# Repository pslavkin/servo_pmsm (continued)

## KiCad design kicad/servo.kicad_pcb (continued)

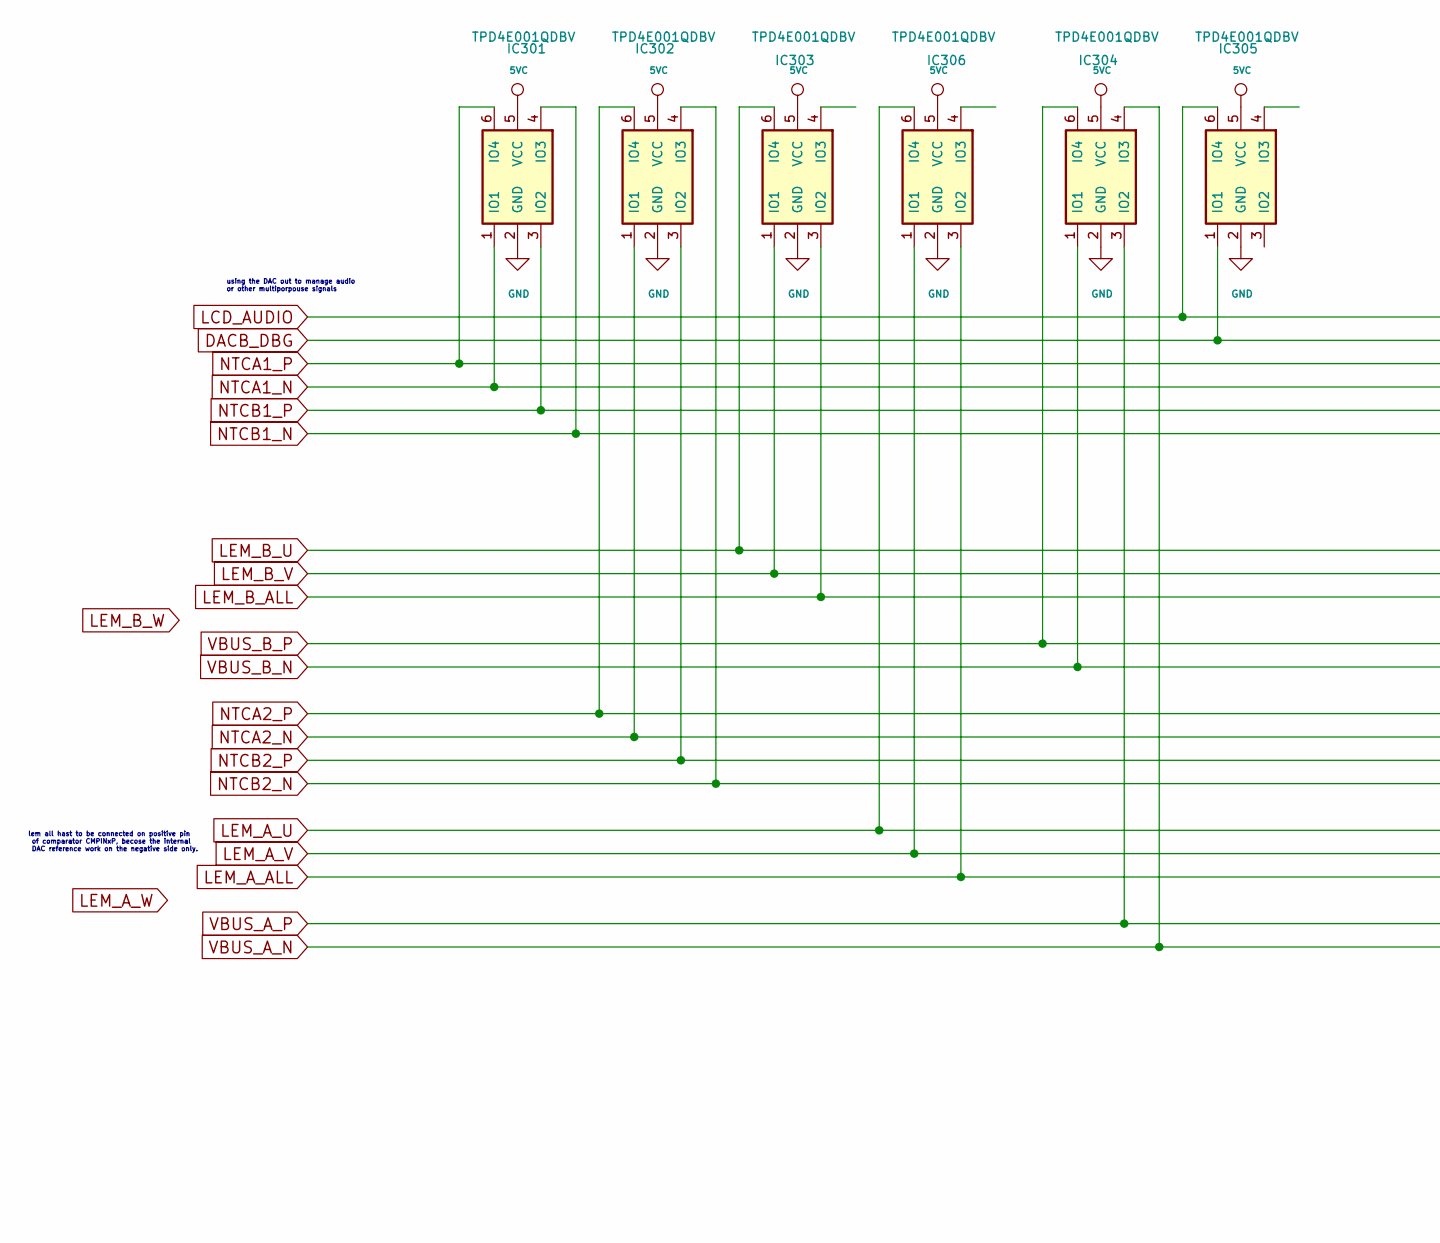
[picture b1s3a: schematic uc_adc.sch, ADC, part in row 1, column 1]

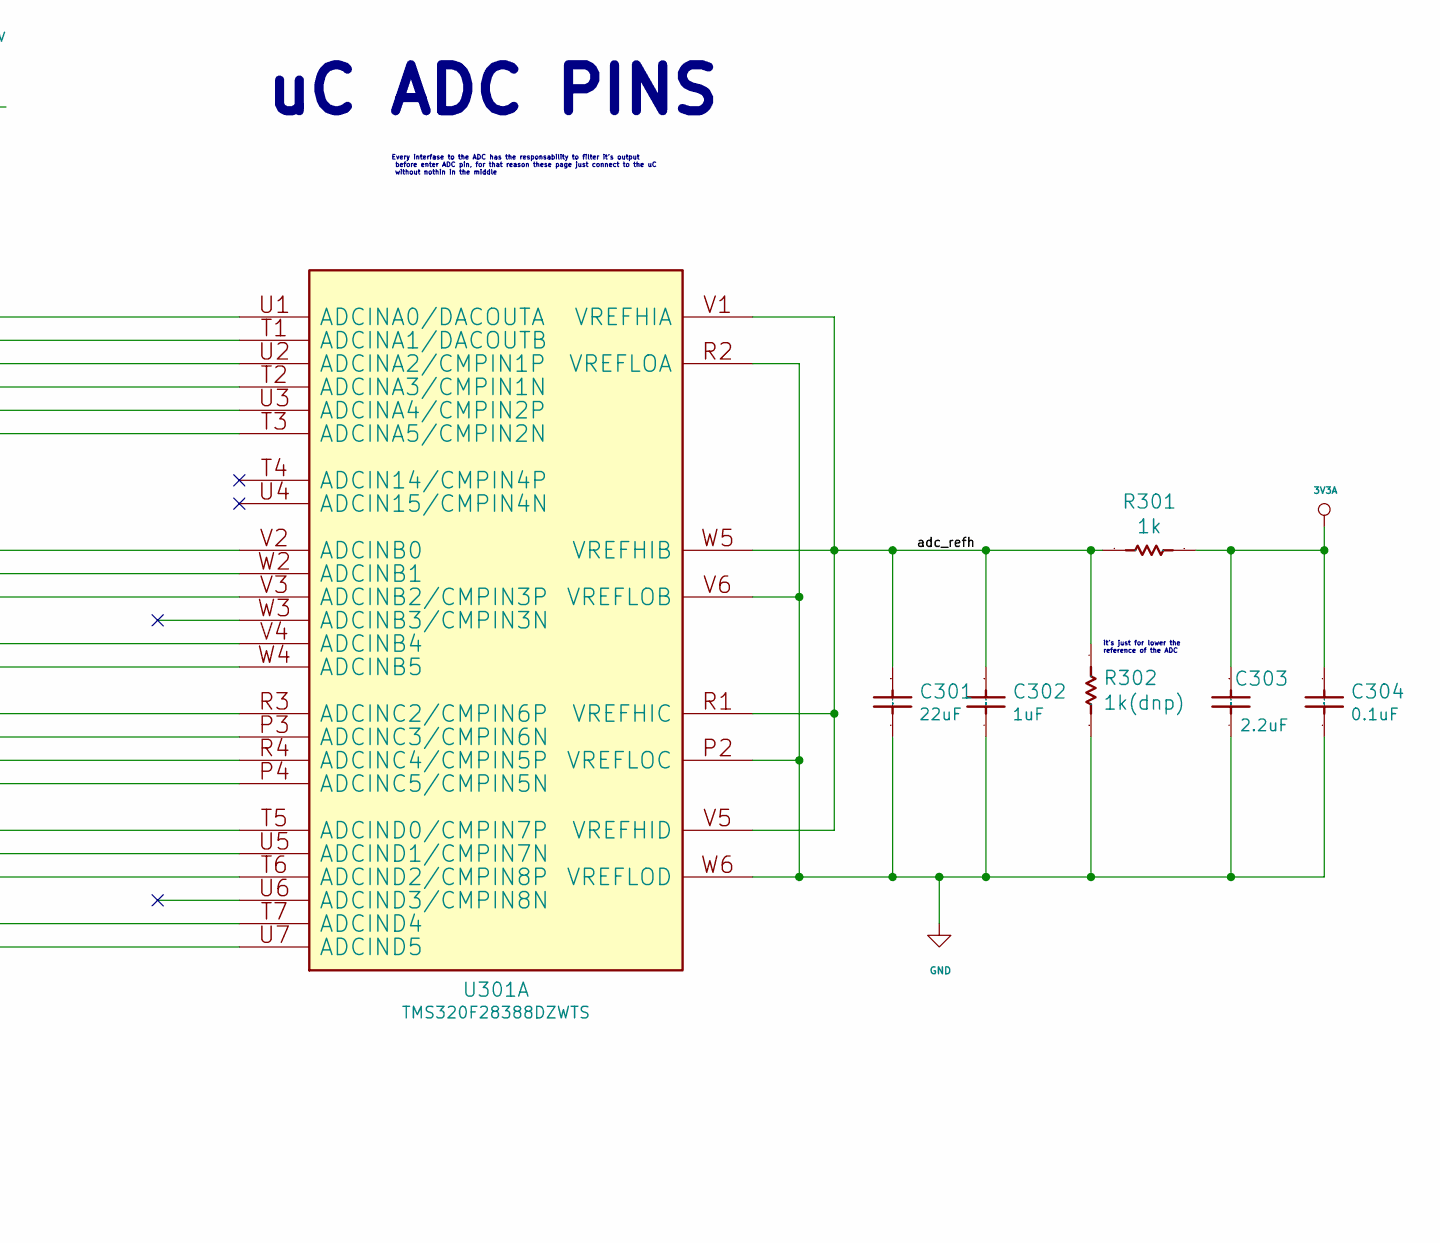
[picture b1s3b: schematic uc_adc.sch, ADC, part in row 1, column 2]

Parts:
C301: 22uF; C_0603_1608Metric
C302: 1uF; C_0603_1608Metric
C303: 2.2uF; C_0603_1608Metric
C304: 0.1uF; C_0603_1608Metric
IC301, IC302, IC303, IC304, IC305, IC306: TPD4E001QDBV; SOT-23-6
R301: 1k; R_0603_1608Metric
R302: 1k(dnp); R_0603_1608Metric
U301: TMS320F28388DZWTS; BGA337CP80_19X19_1600X1600X140B50N; PartNumber TMS320F28388DZWTS

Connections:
3V3A: C303.1, C304.1, R301.1; also elsewhere on the board
5VC: IC301.5 (VCC), IC302.5 (VCC), IC303.5 (VCC), IC304.5 (VCC), IC305.5 (VCC), IC306.5 (VCC); also elsewhere on the board
/uc_adc/adc_refh: C301.1, C302.1, R301.2, R302.2, U301.R1 (VREFHIC), U301.V1 (VREFHIA), U301.V5 (VREFHID), U301.W5 (VREFHIB)
DACB_DBG: IC305.1 (IO1), U301.T1 (ADCINA1/DACOUTB); also elsewhere on the board
GND: C301.2 (Capacitor), C302.2 (Capacitor), C303.2 (Capacitor), C304.2 (Capacitor), IC301.2 (GND), IC302.2 (GND), IC303.2 (GND), IC304.2 (GND), IC305.2 (GND), IC306.2 (GND), R302.1, U301.P2 (VREFLOC), U301.R2 (VREFLOA), U301.V6 (VREFLOB), U301.W6 (VREFLOD); also elsewhere on the board
LCD_AUDIO: IC305.6 (IO4), U301.U1 (ADCINA0/DACOUTA); also elsewhere on the board
LEM_A_ALL: IC306.3 (IO2), U301.T6 (ADCIND2/CMPIN8P); also elsewhere on the board
LEM_A_U: IC306.6 (IO4), U301.T5 (ADCIND0/CMPIN7P); also elsewhere on the board
LEM_A_V: IC306.1 (IO1), U301.U5 (ADCIND1/CMPIN7N); also elsewhere on the board
LEM_B_ALL: IC303.3 (IO2), U301.V3 (ADCINB2/CMPIN3P); also elsewhere on the board
LEM_B_U: IC303.6 (IO4), U301.V2 (ADCINB0); also elsewhere on the board
LEM_B_V: IC303.1 (IO1), U301.W2 (ADCINB1); also elsewhere on the board
NTCA1_N: IC301.1 (IO1), U301.T2 (ADCINA3/CMPIN1N); also elsewhere on the board
NTCA1_P: IC301.6 (IO4), U301.U2 (ADCINA2/CMPIN1P); also elsewhere on the board
NTCA2_N: IC302.1 (IO1), U301.P3 (ADCINC3/CMPIN6N); also elsewhere on the board
NTCA2_P: IC302.6 (IO4), U301.R3 (ADCINC2/CMPIN6P); also elsewhere on the board
NTCB1_N: IC301.4 (IO3), U301.T3 (ADCINA5/CMPIN2N); also elsewhere on the board
NTCB1_P: IC301.3 (IO2), U301.U3 (ADCINA4/CMPIN2P); also elsewhere on the board
NTCB2_N: IC302.4 (IO3), U301.P4 (ADCINC5/CMPIN5N); also elsewhere on the board
NTCB2_P: IC302.3 (IO2), U301.R4 (ADCINC4/CMPIN5P); also elsewhere on the board
VBUS_A_N: IC304.4 (IO3), U301.U7 (ADCIND5); also elsewhere on the board
VBUS_A_P: IC304.3 (IO2), U301.T7 (ADCIND4); also elsewhere on the board
VBUS_B_N: IC304.1 (IO1), U301.W4 (ADCINB5); also elsewhere on the board
VBUS_B_P: IC304.6 (IO4), U301.V4 (ADCINB4); also elsewhere on the board

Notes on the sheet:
lem all hast to be connected on positive pin of comparator CMPINxP, becose the internal DAC reference work on the negative side only.
uC ADC PINS
Every interfase to the ADC has the responsability to filter it's output before enter ADC pin, for that reason these page just connect to the uC without nothin in the middle
using the DAC out to manage audio or other multiporpouse signals
it's just for lower the reference of the ADC

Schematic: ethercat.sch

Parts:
C401, C402, C416, C417: 0.01uF; C_0603_1608Metric
C403, C404, C413, C414, C415, C418, C419, C422, C423: 0.1uF; C_0603_1608Metric
C405, C406, C411, C412, C420, C421, C424, C425, C426, C427, C428, C429, C430, C431, C432, C433: 1uF; C_0603_1608Metric
C407, C408, C409, C410: 10uF; C_0603_1608Metric
C434: 4n7; C_1206_3216Metric
D401: Red@2mA; LED_0603_1608Metric
D402: green@2mA; LED_0603_1608Metric
R401, R402, R403, R404, R405, R406, R407, R408, R409, R410, R411, R412, R413, R414, R415, R416, R427, R433, R434: 2.2k; R_0603_1608Metric
R417, R418: 4.7k; R_0603_1608Metric
R419, R420: 330; R_0603_1608Metric
R421, R424: 4.87k; R_0603_1608Metric
R422, R425: 10.0k; R_0603_1608Metric
R423, R426: 0e; R_0603_1608Metric
R429, R430, R431, R432, R435, R437, R438, R440: 49.9; R_0603_1608Metric
R436, R439: 0e(dnp); R_0603_1608Metric
R441, R442, R445, R446: 470; R_0603_1608Metric
U401: CAT24C16WI; SOIC-8_3.9x4.9mm_P1.27mm
U402, U403: DP83822; QFN-32-1EP_5x5mm_P0.5mm_EP2.9x2.9mm_ThermalVias; PartNumber DP83822IRHBR
U404: rj45x2; rj45x2_0845-2G1T-H5
Y401, Y402: dnp; Oscillator_SMD_SeikoEpson_SG210-4Pin_2.5x2.0mm

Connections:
3V3: C401.2 (Capacitor), C402.2 (Capacitor), C403.2 (Capacitor), C404.2 (Capacitor), C405.1, C406.1, C407.1, C408.1, C409.1, C410.1, C411.1, C412.1, C413.1, C414.1, C415.1, C416.1, C417.1, C418.1, C419.1, C420.1, C421.1, C422.1, C423.1, C424.1, C425.1, C426.2 (Capacitor), C427.2 (Capacitor), C428.2 (Capacitor), C429.2 (Capacitor), C430.2 (Capacitor), C431.2 (Capacitor), C432.2 (Capacitor), C433.2 (Capacitor), R412.1, R413.1, R414.1, R415.1, R416.1, R417.1, R418.1, R419.2, R420.2, R422.2, R425.2, R427.1, R429.1, R430.1, R431.1, R432.1, R433.1, R434.1, R435.1, R437.1, R438.1, R440.1, R441.1, R442.1, R445.1, R446.1, U401.8 (VCC), U402.14 (AVD33), U402.21 (VDDIO), U403.14 (AVD33), U403.21 (VDDIO), U404.2 (TCT), U404.5 (TCT), U404.9 (TCT), U404.12 (TCT), Y401.1 (TRI-STATE), Y401.4 (VCC), Y402.2 (GND), Y402.3 (OUTPUT); also elsewhere on the board
/ethercat/P0_RD_N: R437.2, U402.9 (RD_M), U404.13 (RD-)
/ethercat/P0_RD_P: R435.2, U402.10 (RD_P), U404.11 (RD+)
/ethercat/P0_TD_N: R431.2, U402.11 (TD_M), U404.10 (TD-)
/ethercat/P0_TD_P: R429.2, U402.12 (TD_P), U404.8 (TD+)
/ethercat/P1_RD_N: R440.2, U403.9 (RD_M), U404.6 (RD-)
/ethercat/P1_RD_P: R438.2, U403.10 (RD_P), U404.4 (RD+)
/ethercat/P1_TD_N: R432.2, U403.11 (TD_M), U404.3 (TD-)
/ethercat/P1_TD_P: R430.2, U403.12 (TD_P), U404.1 (TD+)
/ethercat/ecat0_col: R410.2, U402.29 (COL/PHYAD0/MLED)
/ethercat/ecat0_crs: R413.2, U402.27 (CRS/CRS_DV/LED_CFG)
/ethercat/ecat1_col: R412.2, U403.29 (COL/PHYAD0/MLED)
/ethercat/ecat1_crs: R414.2, U403.27 (CRS/CRS_DV/LED_CFG)
ECAT0_RJ_LED0: R436.2, U404.20 (Led-); also elsewhere on the board
ECAT0_RJ_LED1: U404.22 (Led-); also elsewhere on the board
ECAT0_RX_CLK: U402.25 (RX_CLK); also elsewhere on the board
ECAT0_RX_D0: R402.2, U402.30 (RX_D0/PHYAD1); also elsewhere on the board
ECAT0_RX_D1: R404.2, U402.31 (RX_D1/PHYAD2); also elsewhere on the board
ECAT0_RX_D2: R406.2, U402.32 (RX_D2/PHYAD3); also elsewhere on the board
ECAT0_RX_D3: R408.2, U402.1 (RX_D3/PHYAD4/CLKOUT); also elsewhere on the board
ECAT0_RX_DV: R401.2, U402.26 (RX_DV/MII_MODE); also elsewhere on the board
ECAT0_RX_ER: R415.2, U402.28 (RX_ER/AMDIX_EN); also elsewhere on the board
ECAT0_TX_CLK: U402.2 (TX_CLK); also elsewhere on the board
ECAT0_TX_D0: U402.4 (TX_D0); also elsewhere on the board
ECAT0_TX_D1: U402.5 (TX_D1); also elsewhere on the board
ECAT0_TX_D2: U402.6 (TX_D2); also elsewhere on the board
ECAT0_TX_D3: U402.7 (TX_D3); also elsewhere on the board
ECAT0_TX_EN: U402.3 (TX_EN); also elsewhere on the board
ECAT1_RJ_LED0: U404.18 (Led-); also elsewhere on the board
ECAT1_RJ_LED1: R439.2, U404.16 (Led-); also elsewhere on the board
ECAT1_RX_CLK: U403.25 (RX_CLK); also elsewhere on the board
ECAT1_RX_D0: R405.2, U403.30 (RX_D0/PHYAD1); also elsewhere on the board
ECAT1_RX_D1: R407.2, U403.31 (RX_D1/PHYAD2); also elsewhere on the board
ECAT1_RX_D2: R409.2, U403.32 (RX_D2/PHYAD3); also elsewhere on the board
ECAT1_RX_D3: R411.2, U403.1 (RX_D3/PHYAD4/CLKOUT); also elsewhere on the board
ECAT1_RX_DV: R403.2, U403.26 (RX_DV/MII_MODE); also elsewhere on the board
ECAT1_RX_ER: R416.2, U403.28 (RX_ER/AMDIX_EN); also elsewhere on the board
ECAT1_TX_CLK: U403.2 (TX_CLK); also elsewhere on the board
ECAT1_TX_D0: U403.4 (TX_D0); also elsewhere on the board
ECAT1_TX_D1: U403.5 (TX_D1); also elsewhere on the board
ECAT1_TX_D2: U403.6 (TX_D2); also elsewhere on the board
ECAT1_TX_D3: U403.7 (TX_D3); also elsewhere on the board
ECAT1_TX_EN: U403.3 (TX_EN); also elsewhere on the board
ECAT_EEPROM_SCL: R418.2, U401.6 (SCL); also elsewhere on the board
ECAT_EEPROM_SDA: R417.2, U401.5 (SDA); also elsewhere on the board
ECAT_LED_ERR: D402.1 (K); also elsewhere on the board
ECAT_LED_RUN: D401.1 (K); also elsewhere on the board
ECAT_MDCLK: U402.20 (MDC), U403.20 (MDC); also elsewhere on the board
ECAT_MDIO: R427.2, U402.19 (MDIO), U403.19 (MDIO); also elsewhere on the board
ECAT_RST: U402.18 (RESET), U403.18 (RESET); also elsewhere on the board
ENET_CAT_XI: R423.2, R426.2; also elsewhere on the board
Earth: C434.2 (Capacitor), U404.7 (Gnd), U404.14 (Gnd); also elsewhere on the board
GND: C401.1, C402.1, C403.1, C404.1, C405.2 (Capacitor), C406.2 (Capacitor), C407.2 (Capacitor), C408.2 (Capacitor), C409.2 (Capacitor), C410.2 (Capacitor), C411.2 (Capacitor), C412.2 (Capacitor), C413.2 (Capacitor), C414.2 (Capacitor), C415.2 (Capacitor), C416.2 (Capacitor), C417.2 (Capacitor), C418.2 (Capacitor), C419.2 (Capacitor), C420.2 (Capacitor), C421.2 (Capacitor), C422.2 (Capacitor), C423.2 (Capacitor), C424.2 (Capacitor), C425.2 (Capacitor), C426.1, C427.1, C428.1, C429.1, C430.1, C431.1, C432.1, C433.1, C434.1, R401.1, R402.1, R403.1, R404.1, R405.1, R406.1, R407.1, R408.1, R409.1, R410.1, R411.1, R421.2, R424.2, U401.1 (NC), U401.2 (NC), U401.3 (NC), U401.4 (VSS), U401.7 (WP), U402.33 (PAD), U403.33 (PAD), Y401.2 (GND), Y402.1 (TRI-STATE); also elsewhere on the board
unnamed: D401.2 (A), R419.1
unnamed: D402.2 (A), R420.1
unnamed: R421.1, U402.16 (RBIAS)
unnamed: R422.1, U402.8 (INT/~PWDN)
unnamed: R423.1, U402.23 (XI), Y401.3 (OUTPUT)
unnamed: R424.1, U403.16 (RBIAS)
unnamed: R425.1, U403.8 (INT/~PWDN)
unnamed: R426.1, U403.23 (XI), Y402.4 (VCC)
unnamed: R433.2, R436.1, U402.17 (LED_0/AN_0/MLED)
unnamed: R434.2, R439.1, U403.17 (LED_0/AN_0/MLED)
unnamed: R441.2, U404.17 (Led+)
unnamed: R442.2, U404.15 (Led+)
unnamed: R445.2, U404.21 (Led+)
unnamed: R446.2, U404.19 (Led+)

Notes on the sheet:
EtherCAT P1
EtherCAT EEPROM
Run and Error LEDs
EtherCAT P0
Address select. Be shure you select two distinct
these IC is a 'must'. Especified on the ethercat slave
EtherCAT
you could choose between uC out clk, oscilator for ecah PHY or share oscilator to many PHY's using uC out clk path
the pullup of led_0 is mandatory, but to drive the led you could choose between PHY or uC populating/unpopulating the resistor
It'd be optionall
I choose transfeormer spare part instead of the embedded shielded RJ45 plus leds, cause noy I can choose any format connector RJ45 and maybe add PoE then. And are halt the price The eeprom is mandatory in order to ESC read save some internal configuration. Leds are optional, but the PHY's has som p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
2k2 pullup as indicated by phy IC's
25Mhz!!
It's a good idea to have them on these fitst stage but could be throught away on next release.

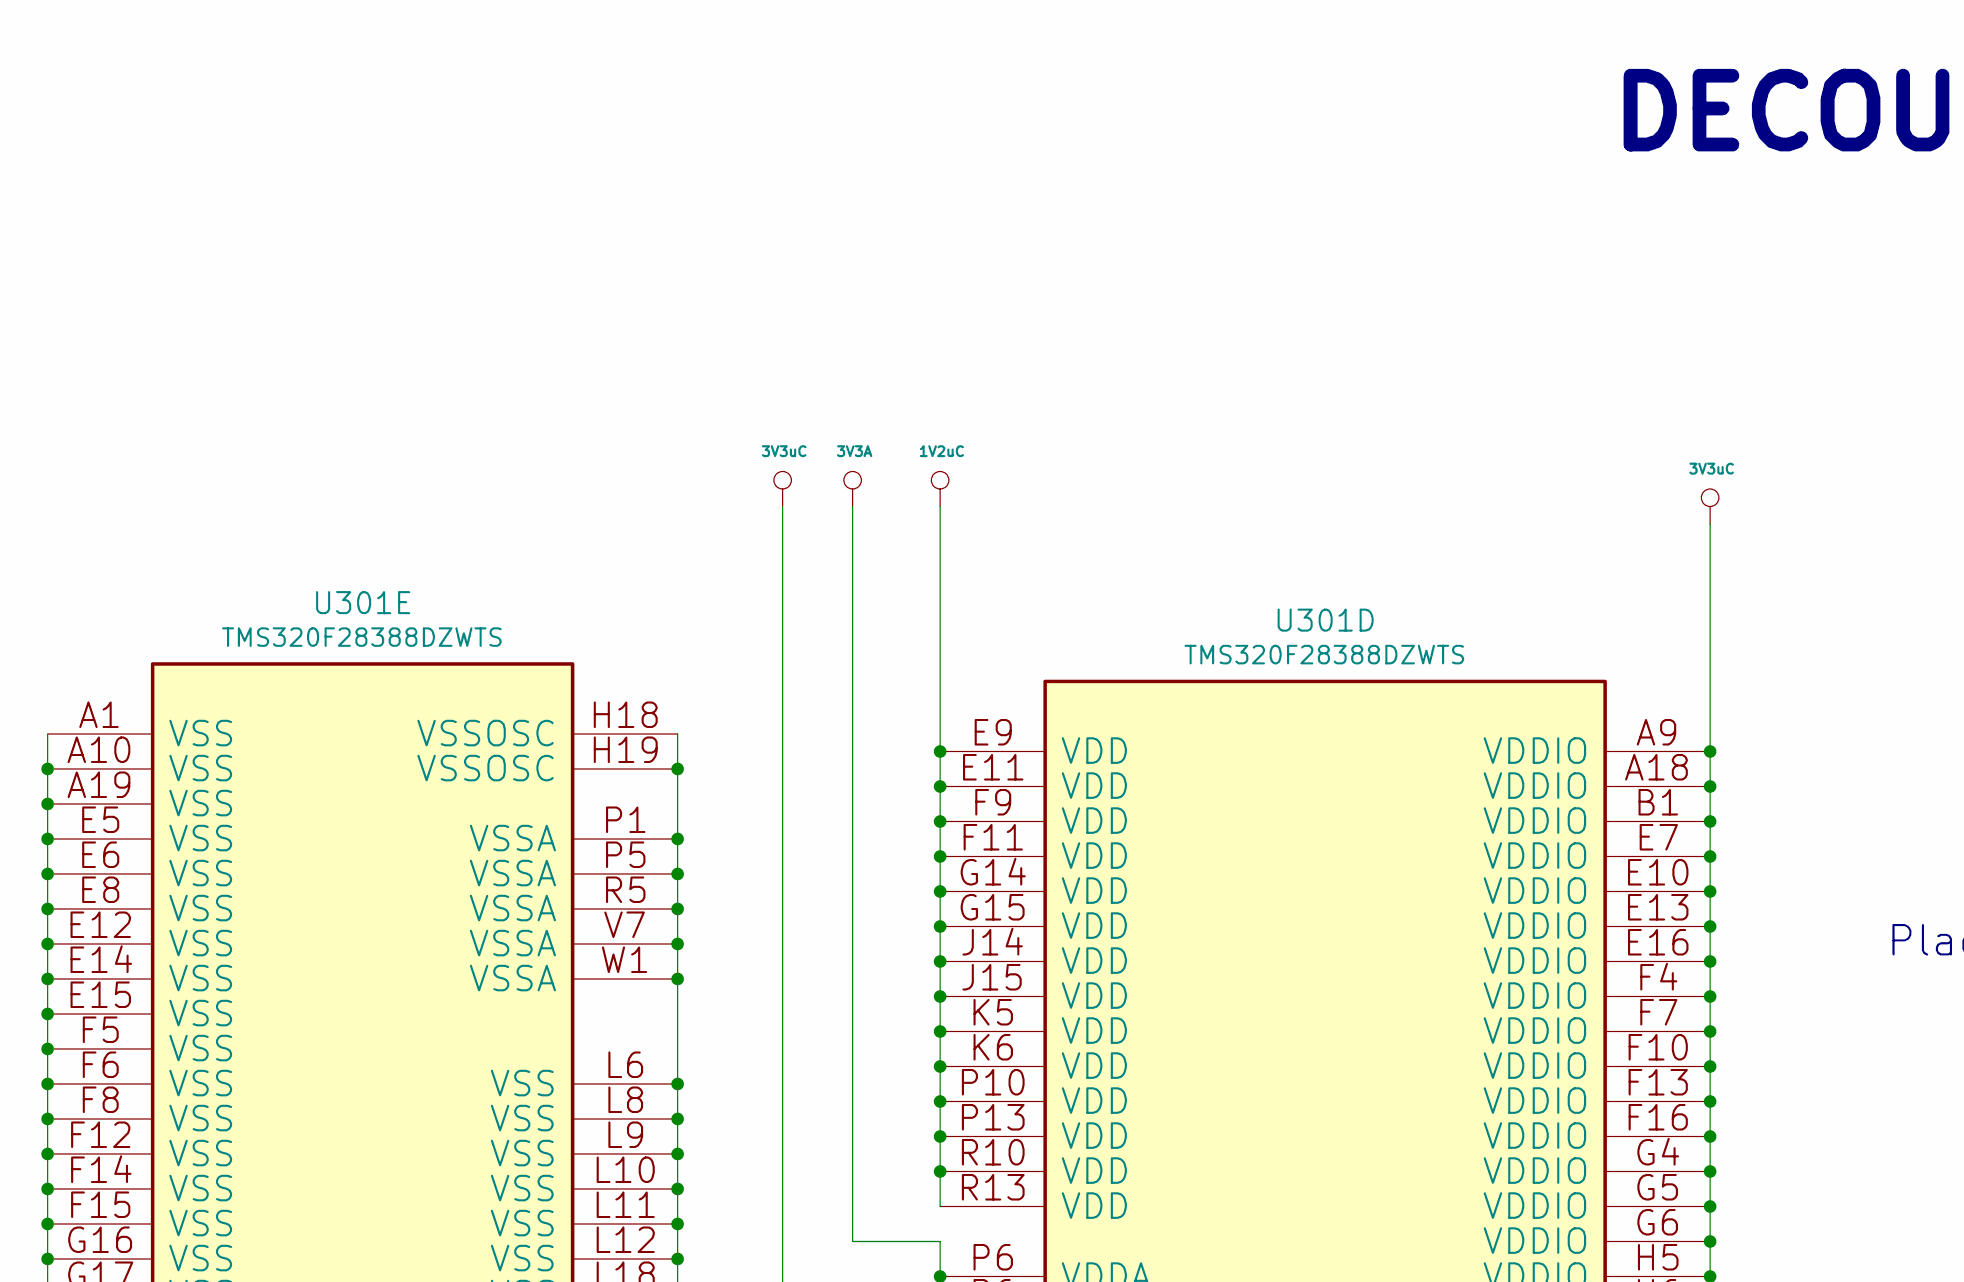
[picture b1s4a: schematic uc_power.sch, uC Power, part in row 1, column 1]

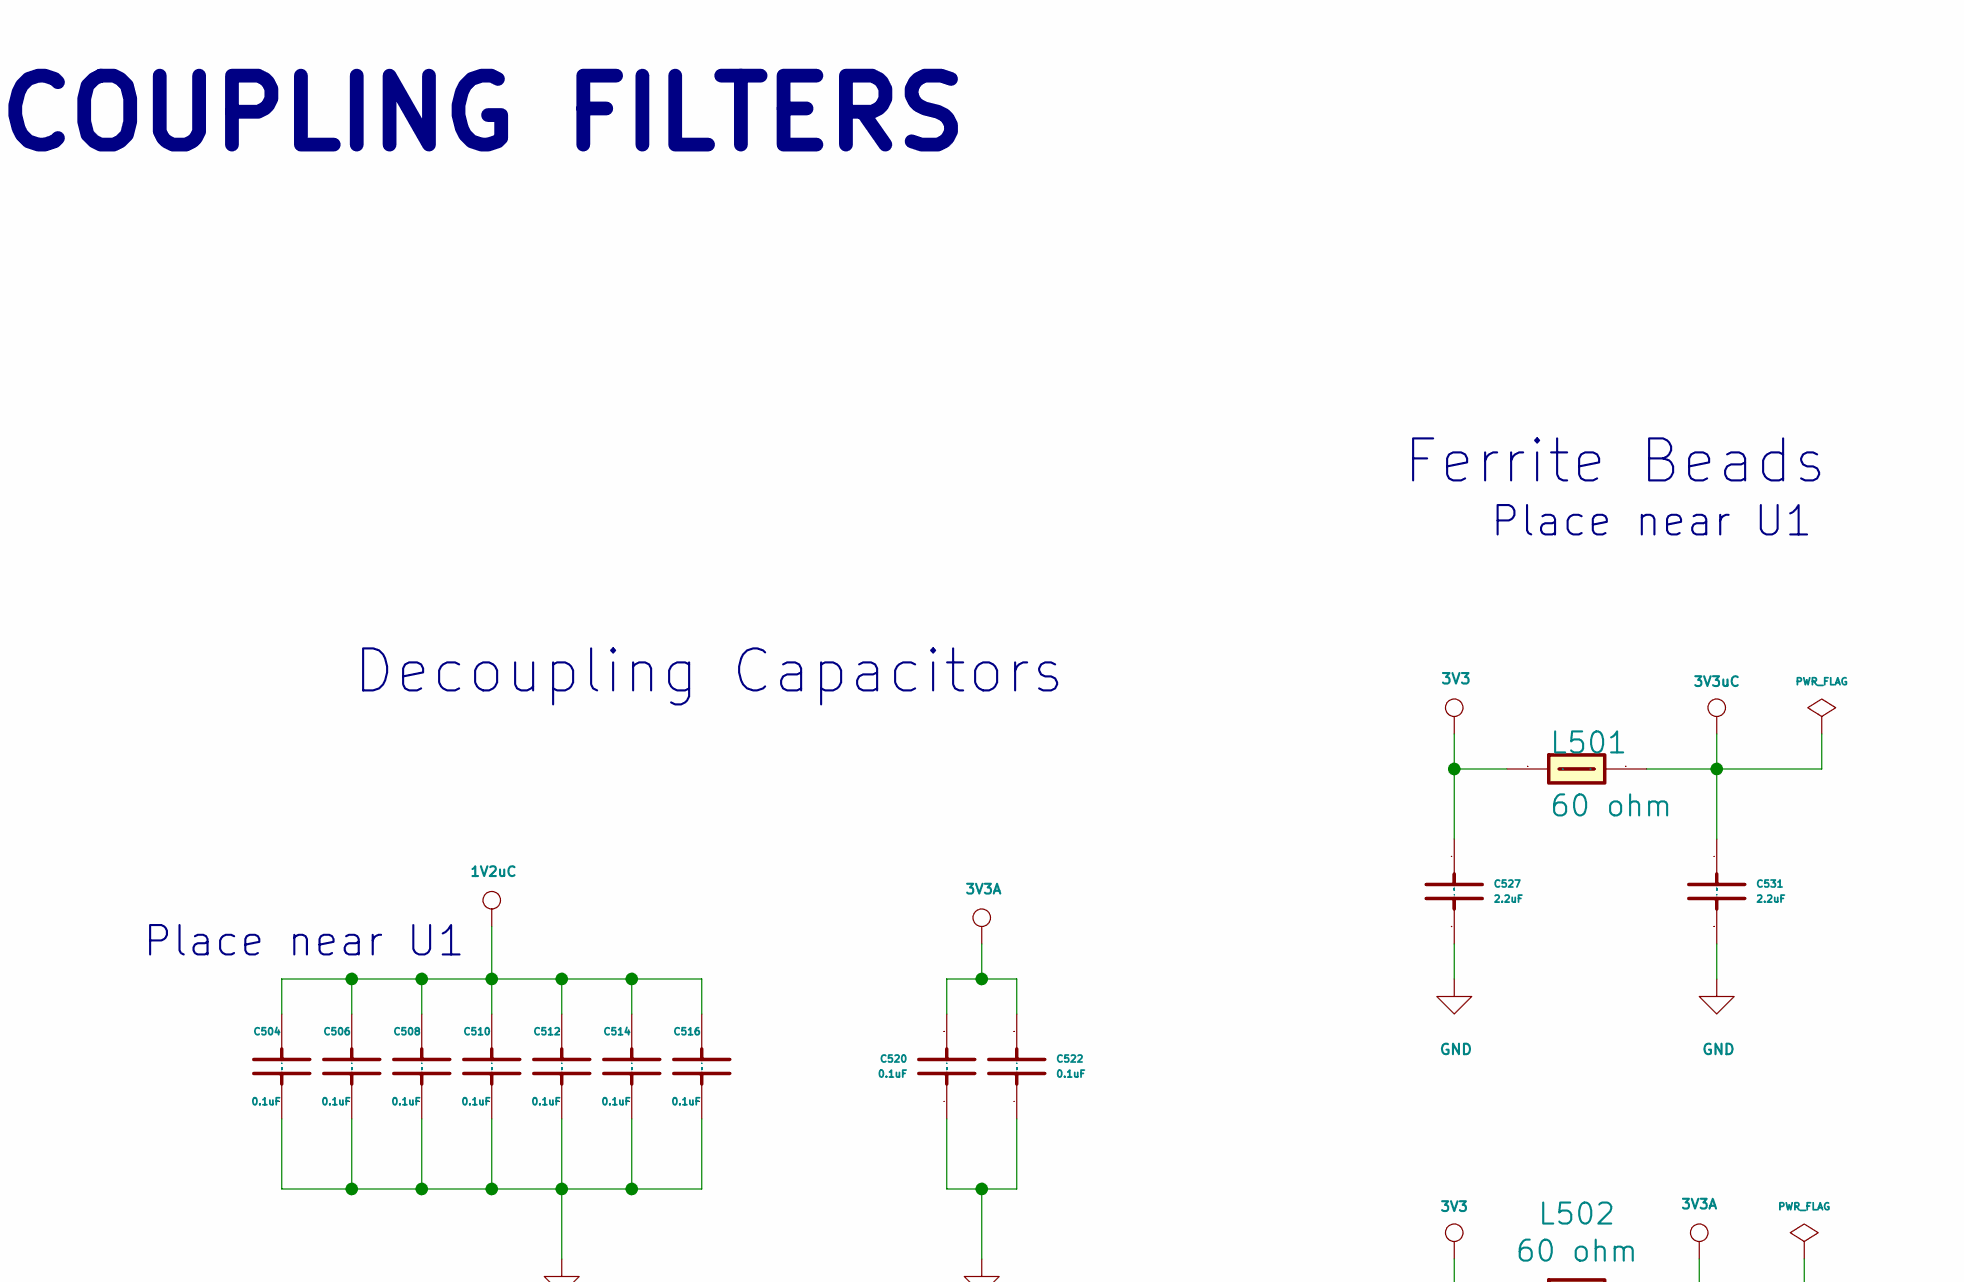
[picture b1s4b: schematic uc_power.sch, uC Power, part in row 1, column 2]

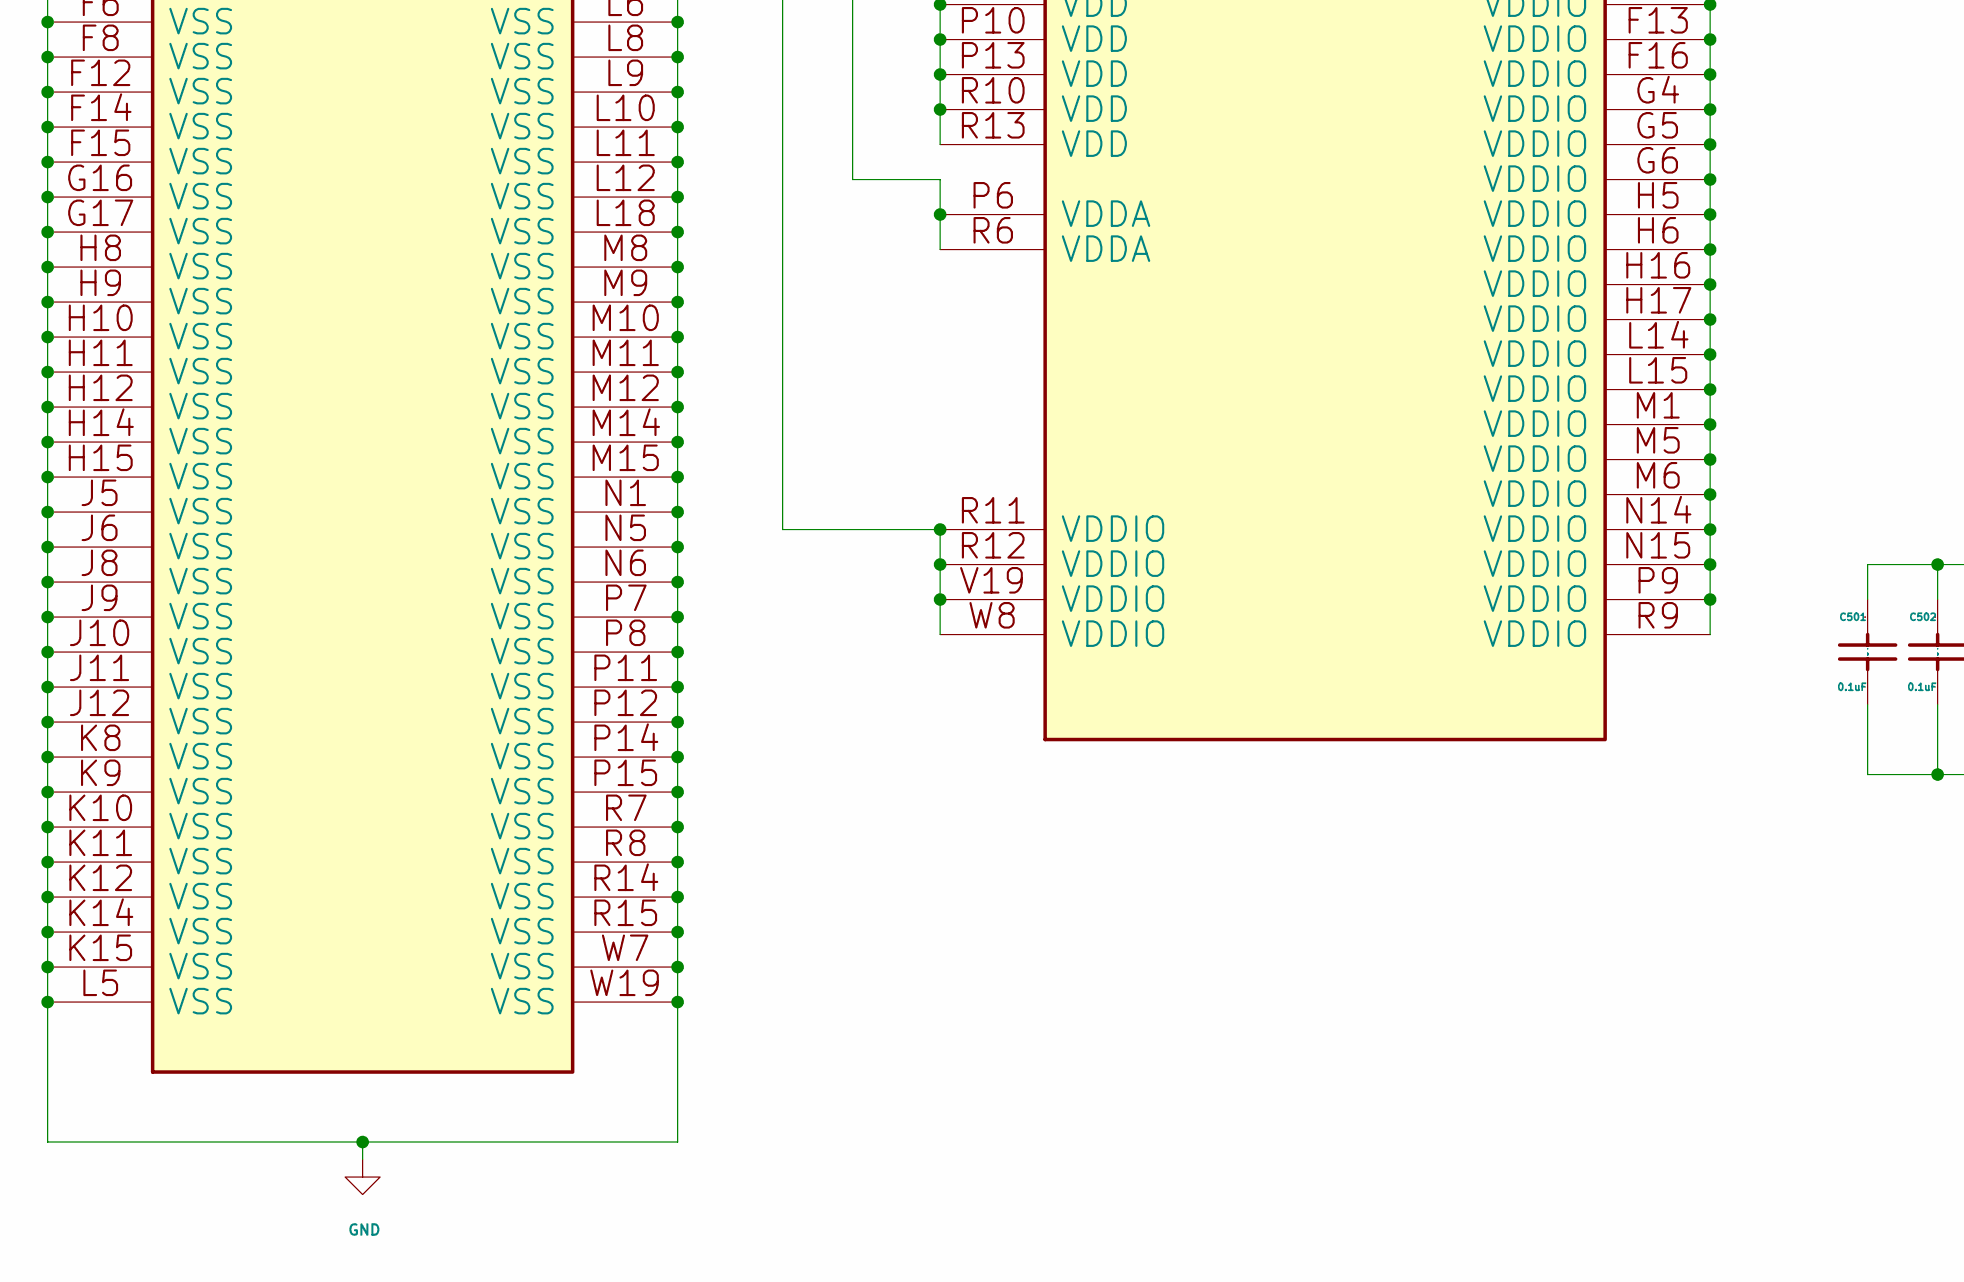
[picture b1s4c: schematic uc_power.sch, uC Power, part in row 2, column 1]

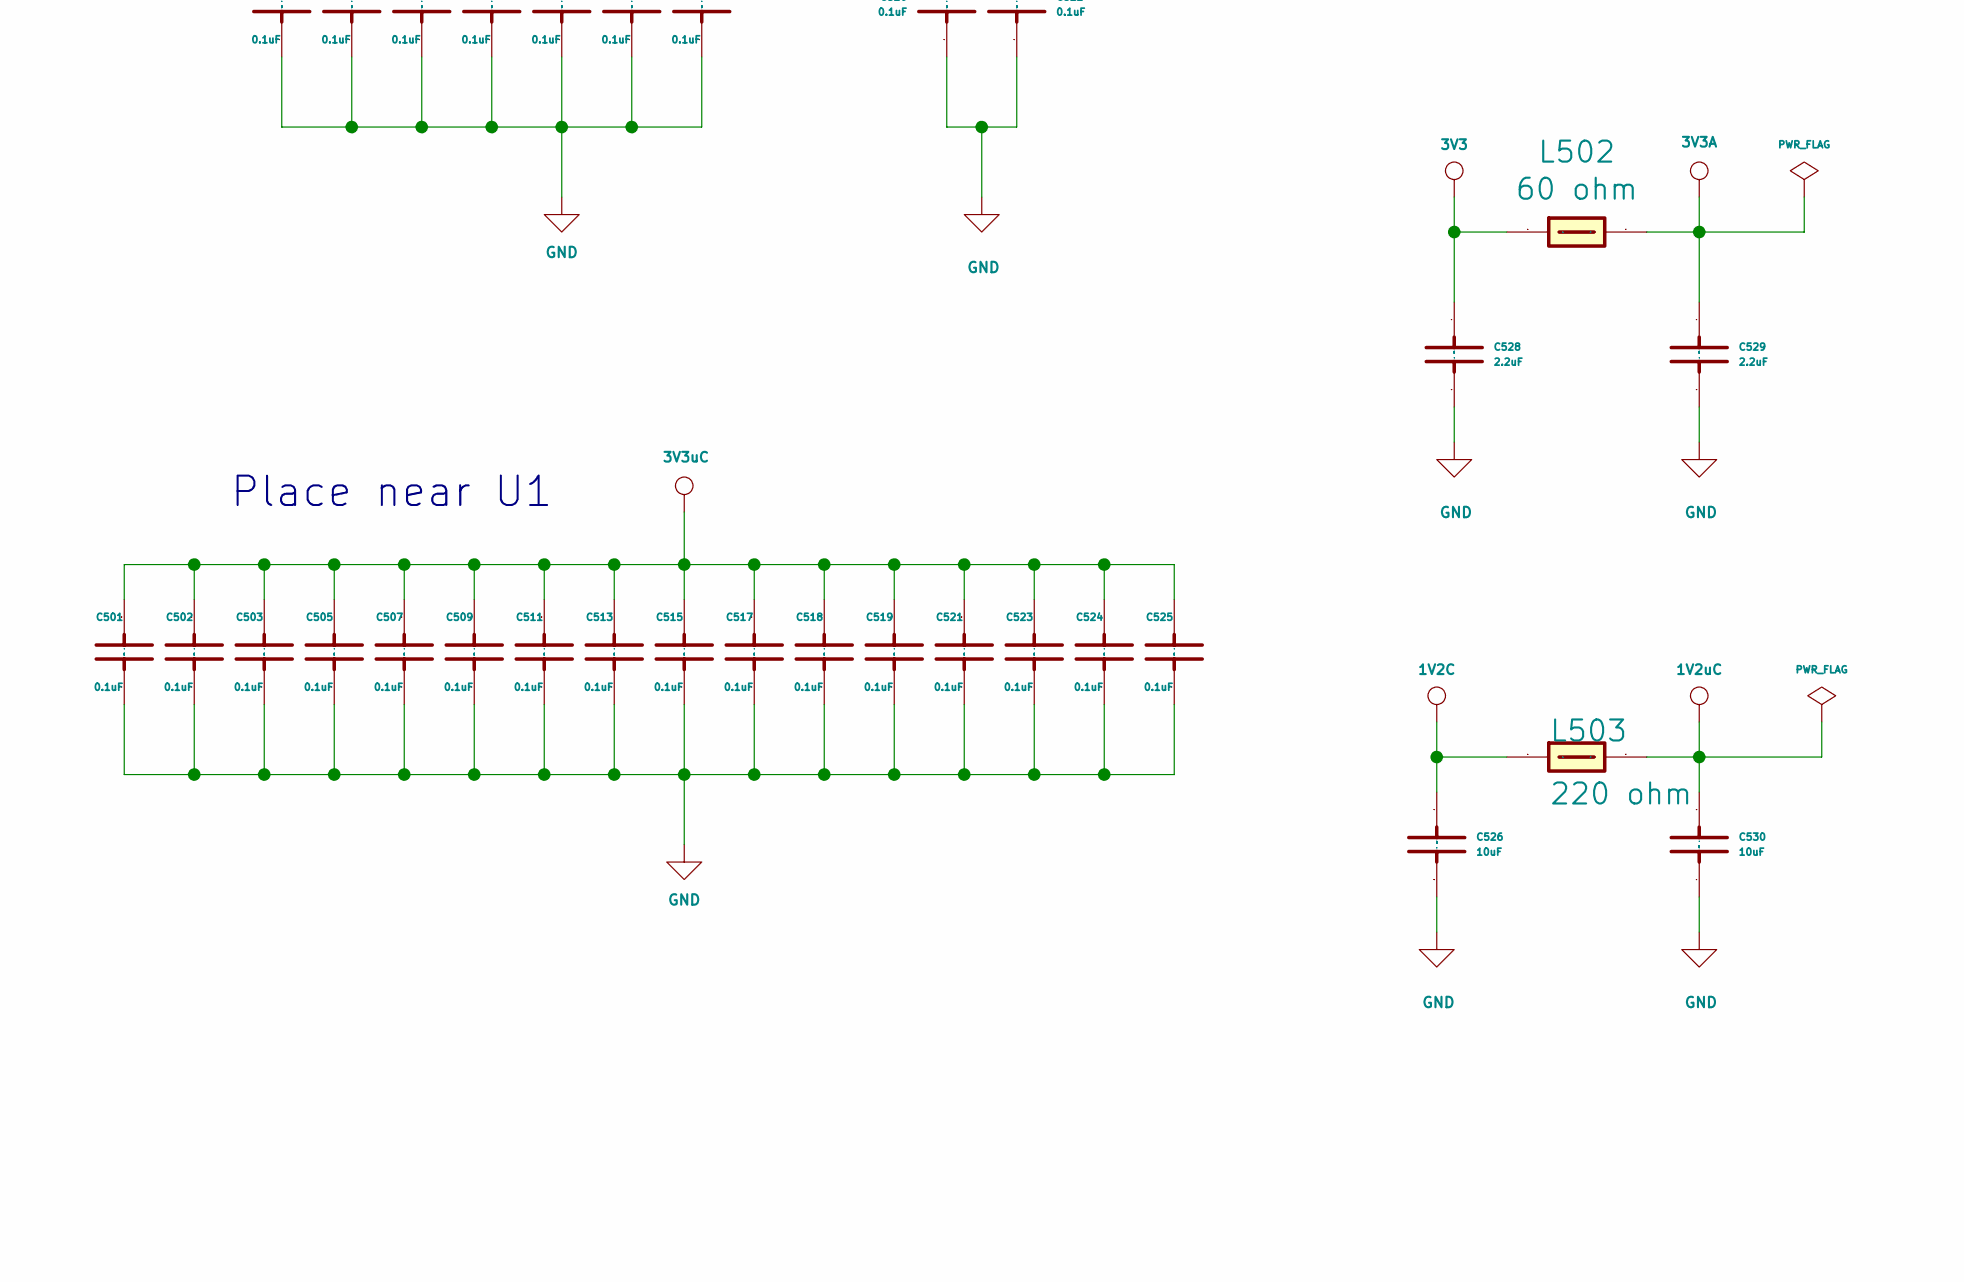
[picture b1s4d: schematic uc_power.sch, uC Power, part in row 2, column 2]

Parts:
C501, C502, C503, C504, C505, C506, C507, C508, C509, C510, C511, C512, C513, C514, C515, C516, C517, C518, C519, C520, C521, C522, C523, C524, C525: 0.1uF; C_0603_1608Metric
C526, C530: 10uF; C_0603_1608Metric
C527, C528, C529, C531: 2.2uF; C_0603_1608Metric
L501, L502: 60 ohm; L_1206_3216Metric_Pad1.42x1.75mm_HandSolder
L503: 220 ohm; L_1206_3216Metric_Pad1.42x1.75mm_HandSolder
U301: TMS320F28388DZWTS; BGA337CP80_19X19_1600X1600X140B50N; PartNumber TMS320F28388DZWTS

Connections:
1V2: C504.1, C506.1, C508.1, C510.1, C512.1, C514.1, C516.1, C530.1, L503.2, U301.E9 (VDD), U301.E11 (VDD), U301.F9 (VDD), U301.F11 (VDD), U301.G14 (VDD), U301.G15 (VDD), U301.J14 (VDD), U301.J15 (VDD), U301.K5 (VDD), U301.K6 (VDD), U301.P10 (VDD), U301.P13 (VDD), U301.R10 (VDD), U301.R13 (VDD)
1V2C: C526.2 (Capacitor), L503.1; also elsewhere on the board
3V3: C527.2 (Capacitor), C528.2 (Capacitor), L501.1, L502.1; also elsewhere on the board
3V3A: C520.1, C522.1, C529.2 (Capacitor), L502.2, U301.P6 (VDDA), U301.R6 (VDDA); also elsewhere on the board
GND: C501.2 (Capacitor), C502.2 (Capacitor), C503.2 (Capacitor), C504.2 (Capacitor), C505.2 (Capacitor), C506.2 (Capacitor), C507.2 (Capacitor), C508.2 (Capacitor), C509.2 (Capacitor), C510.2 (Capacitor), C511.2 (Capacitor), C512.2 (Capacitor), C513.2 (Capacitor), C514.2 (Capacitor), C515.2 (Capacitor), C516.2 (Capacitor), C517.2 (Capacitor), C518.2 (Capacitor), C519.2 (Capacitor), C520.2 (Capacitor), C521.2 (Capacitor), C522.2 (Capacitor), C523.2 (Capacitor), C524.2 (Capacitor), C525.2 (Capacitor), C526.1, C527.1, C528.1, C529.1, C530.2 (Capacitor), C531.1, U301.A1 (VSS), U301.A10 (VSS), U301.A19 (VSS), U301.E5 (VSS), U301.E6 (VSS), U301.E8 (VSS), U301.E12 (VSS), U301.E14 (VSS), U301.E15 (VSS), U301.F5 (VSS), U301.F6 (VSS), U301.F8 (VSS), U301.F12 (VSS), U301.F14 (VSS), U301.F15 (VSS), U301.G16 (VSS), U301.G17 (VSS), U301.H8 (VSS), U301.H9 (VSS), U301.H10 (VSS), U301.H11 (VSS), U301.H12 (VSS), U301.H14 (VSS), U301.H15 (VSS), U301.H18 (VSSOSC), U301.H19 (VSSOSC), U301.J5 (VSS), U301.J6 (VSS), U301.J8 (VSS), U301.J9 (VSS), U301.J10 (VSS), U301.J11 (VSS), U301.J12 (VSS), U301.K8 (VSS), U301.K9 (VSS), U301.K10 (VSS), U301.K11 (VSS), U301.K12 (VSS), U301.K14 (VSS), U301.K15 (VSS), U301.L5 (VSS), U301.L6 (VSS), U301.L8 (VSS), U301.L9 (VSS), U301.L10 (VSS), U301.L11 (VSS), U301.L12 (VSS), U301.L18 (VSS), U301.M8 (VSS), U301.M9 (VSS), U301.M10 (VSS), U301.M11 (VSS), U301.M12 (VSS), U301.M14 (VSS), U301.M15 (VSS), U301.N1 (VSS), U301.N5 (VSS), U301.N6 (VSS), U301.P1 (VSSA), U301.P5 (VSSA), U301.P7 (VSS), U301.P8 (VSS), U301.P11 (VSS), U301.P12 (VSS), U301.P14 (VSS), U301.P15 (VSS), U301.R5 (VSSA), U301.R7 (VSS), U301.R8 (VSS), U301.R14 (VSS), U301.R15 (VSS), U301.V7 (VSSA), U301.W1 (VSSA), U301.W7 (VSS), U301.W19 (VSS); also elsewhere on the board
IN_3V3C: C501.1, C502.1, C503.1, C505.1, C507.1, C509.1, C511.1, C513.1, C515.1, C517.1, C518.1, C519.1, C521.1, C523.1, C524.1, C525.1, C531.2 (Capacitor), L501.2, U301.A9 (VDDIO), U301.A18 (VDDIO), U301.B1 (VDDIO), U301.E7 (VDDIO), U301.E10 (VDDIO), U301.E13 (VDDIO), U301.E16 (VDDIO), U301.F4 (VDDIO), U301.F7 (VDDIO), U301.F10 (VDDIO), U301.F13 (VDDIO), U301.F16 (VDDIO), U301.G4 (VDDIO), U301.G5 (VDDIO), U301.G6 (VDDIO), U301.H5 (VDDIO), U301.H6 (VDDIO), U301.H16 (VDDIO), U301.H17 (VDDIO), U301.L14 (VDDIO), U301.L15 (VDDIO), U301.M1 (VDDIO), U301.M5 (VDDIO), U301.M6 (VDDIO), U301.N14 (VDDIO), U301.N15 (VDDIO), U301.P9 (VDDIO), U301.R9 (VDDIO), U301.R11 (VDDIO), U301.R12 (VDDIO), U301.V19 (VDDIO), U301.W8 (VDDIO)

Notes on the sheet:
Place near U1
Decoupling Capacitors
Ferrite Beads
DECOUPLING FILTERS
